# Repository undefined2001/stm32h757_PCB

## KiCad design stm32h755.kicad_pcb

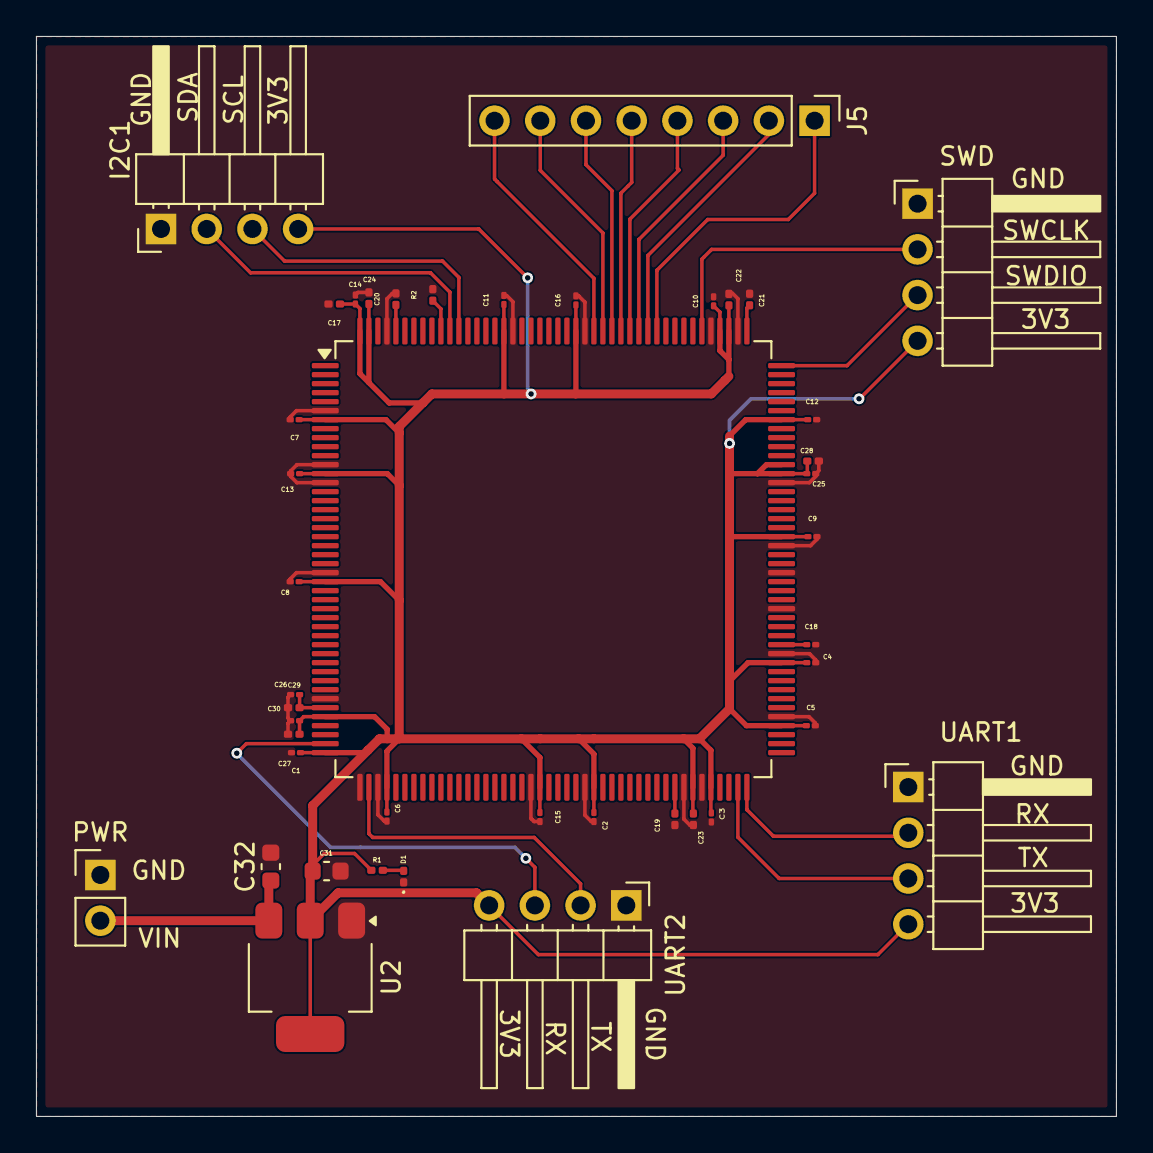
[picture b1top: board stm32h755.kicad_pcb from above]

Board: 2 copper layers, 60.0 x 60.0 mm, 43 parts (0 on the bottom side), 26 nets.

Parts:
C1, C2, C3, C4, C5, C6, C7, C8, C9, C10, C11, C12, C13, C14, C15, C16, C25, C26, C29: 100nF; C_01005_0402Metric
C17, C22, C23, C24: 4u7; C_0201_0603Metric
C18: 2u2; C_01005_0402Metric
C19, C20, C21: 2u2; C_0201_0603Metric
C27, C28, C30: 1uF; C_0201_0603Metric
C31, C32: 10uF; C_0603_1608Metric
D1: LED; LED_0201_0603Metric
I2C1: Conn_01x04_Pin; PinHeader_1x04_P2.54mm_Horizontal
J5: Conn_01x08_Pin; PinHeader_1x08_P2.54mm_Vertical
PWR: Conn_01x02_Pin; PinHeader_1x02_P2.54mm_Vertical
R1: 10K; R_0201_0603Metric
R2: R; R_0201_0603Metric
SWD: Conn_01x04_Pin; PinHeader_1x04_P2.54mm_Horizontal
U1: STM32H757IITx; LQFP-176_24x24mm_P0.5mm
U2: AMS1117; SOT-223-3_TabPin2
UART1, UART2: Conn_01x04_Pin; PinHeader_1x04_P2.54mm_Horizontal

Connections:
+3V3: C1.1, C2.1, C3.1, C4.1, C5.1, C6.1, C7.1, C8.1, C9.1, C10.1, C11.1, C12.1, C13.1, C14.1, C15.1, C16.1, C17.1, C22.1, C23.1, C24.1, C25.1, C26.1, C27.1, C28.1, C31.1, I2C1.4, R1.2, SWD.4, U1.7 (VDD), U1.13 (VDD), U1.25 (VDD), U1.40 (VDDA), U1.44 (VDD), U1.48 (VDD), U1.65 (VDD), U1.71 (VDD), U1.82 (VDDLDO), U1.84 (VDD), U1.92 (VDD), U1.99 (VDD), U1.113 (VDD), U1.120 (VDD50_USB), U1.121 (VDD33_USB), U1.126 (VDD), U1.135 (VDDLDO), U1.136 (VDD), U1.152 (VDD), U1.160 (VDD), U1.175 (VDDLDO), U1.176 (VDD), U2.2 (VO), UART1.4, UART2.4
+5V: C32.1, PWR.2, U2.3 (VI)
/VREF: C29.1, C30.1, U1.39 (VREF+)
GND: C1.2, C2.2, C3.2, C4.2, C5.2, C6.2, C7.2, C8.2, C9.2, C10.2, C11.2, C12.2, C13.2, C14.2, C15.2, C16.2, C17.2, C18.2, C19.2, C20.2, C21.2, C22.2, C23.2, C24.2, C25.2, C26.2, C27.2, C28.2, C29.2, C30.2, C31.2, C32.2, D1.1 (K), I2C1.1, PWR.1, R2.2, SWD.1, U1.6 (VSS), U1.12 (VSS), U1.14 (VSSSMPS), U1.24 (VSS), U1.38 (VSSA), U1.45 (VSS), U1.47 (VSS), U1.64 (VSS), U1.70 (VSS), U1.81 (VSS), U1.83 (VSS), U1.93 (VSS), U1.100 (VSS), U1.105 (VSSDSI), U1.109 (VSSDSI), U1.112 (VSS), U1.119 (VSS), U1.134 (VSS), U1.137 (VSS), U1.151 (VSS), U1.159 (VSS), U1.173 (VSS), U2.1 (ADJ), UART1.1, UART2.1
unnamed: C19.1, U1.80 (VCAP)
unnamed: C20.1, U1.172 (VCAP)
unnamed: C21.1, U1.133 (VCAP)
unnamed: D1.2 (A), R1.1
unnamed: SWD.2, U1.138 (PA14)
unnamed: SWD.3, U1.132 (PA13)
unnamed: U1.46 (PA3), UART2.2
unnamed: U1.43 (PA2), UART2.3
unnamed: U1.88 (PB15), UART1.2
unnamed: U1.87 (PB14), UART1.3
unnamed: I2C1.2, U1.166 (PB7)
unnamed: I2C1.3, U1.165 (PB6)
unnamed: J5.1, U1.143 (PD0)
unnamed: J5.2, U1.144 (PD1)
unnamed: J5.3, U1.145 (PD2)
unnamed: J5.4, U1.146 (PD3)
unnamed: J5.5, U1.147 (PD4)
unnamed: J5.6, U1.148 (PD5)
unnamed: J5.7, U1.149 (PD6)
unnamed: J5.8, U1.150 (PD7)
unnamed: R2.1, U1.167 (BOOT0)
unnamed: C18.1, U1.101 (VCAPDSI)

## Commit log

2025-04-21 Decoupling Capacitors Placed
2025-04-21 Redesigned PCB
